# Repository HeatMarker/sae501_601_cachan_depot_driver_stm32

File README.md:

# Projet STM32

Ce dépôt contient l'intégralité du code source et la documentation pour le projet STM32.

## Structure du projet

* **Racine** : Contient le projet STM32 complet (fichiers sources, includes, configuration).
* **datasheet/** : Contient la documentation technique générée (Doxygen/Datasheet).

---

## Documentation

La documentation se trouve dans le dossier `datasheet/`. Deux formats sont proposés, mais la **version HTML est fortement recommandée** pour la navigation.

### 1. Version HTML (Recommandée) 
Format le plus pratique pour explorer le code et les fonctions.

* **Emplacement :** Ouvrir le fichier `index.html` situé dans le dossier `datasheet/html/`.
* **⚠️ Attention à l'affichage :**
    > Si le texte est illisible ou apparaît "noir sur noir", cela est probablement dû à une extension de mode sombre (Dark Reader, Dark Mode natif, etc.).
    > **Désactiver le mode sombre du navigateur** pour consulter cette documentation correctement.

### 2. Version PDF
Une version PDF est normalement disponible à la racine du dossier `datasheet/`.

**Si le fichier PDF n'est pas présent**, il est nécessaire de le générer via LaTeX :

1.  Se rendre dans le dossier : `datasheet/latex/`
2.  Compiler le fichier source : `refman.tex`
3.  Le fichier généré sera disponible ici : `datasheet/latex/refman.pdf`

---

## Utilisation

1.  Cloner ce dépôt.
2.  Ouvrir le projet avec l'IDE habituel (ex: STM32CubeIDE).
3.  Consulter la documentation HTML dans `datasheet/html/` pour les détails d'implémentation.

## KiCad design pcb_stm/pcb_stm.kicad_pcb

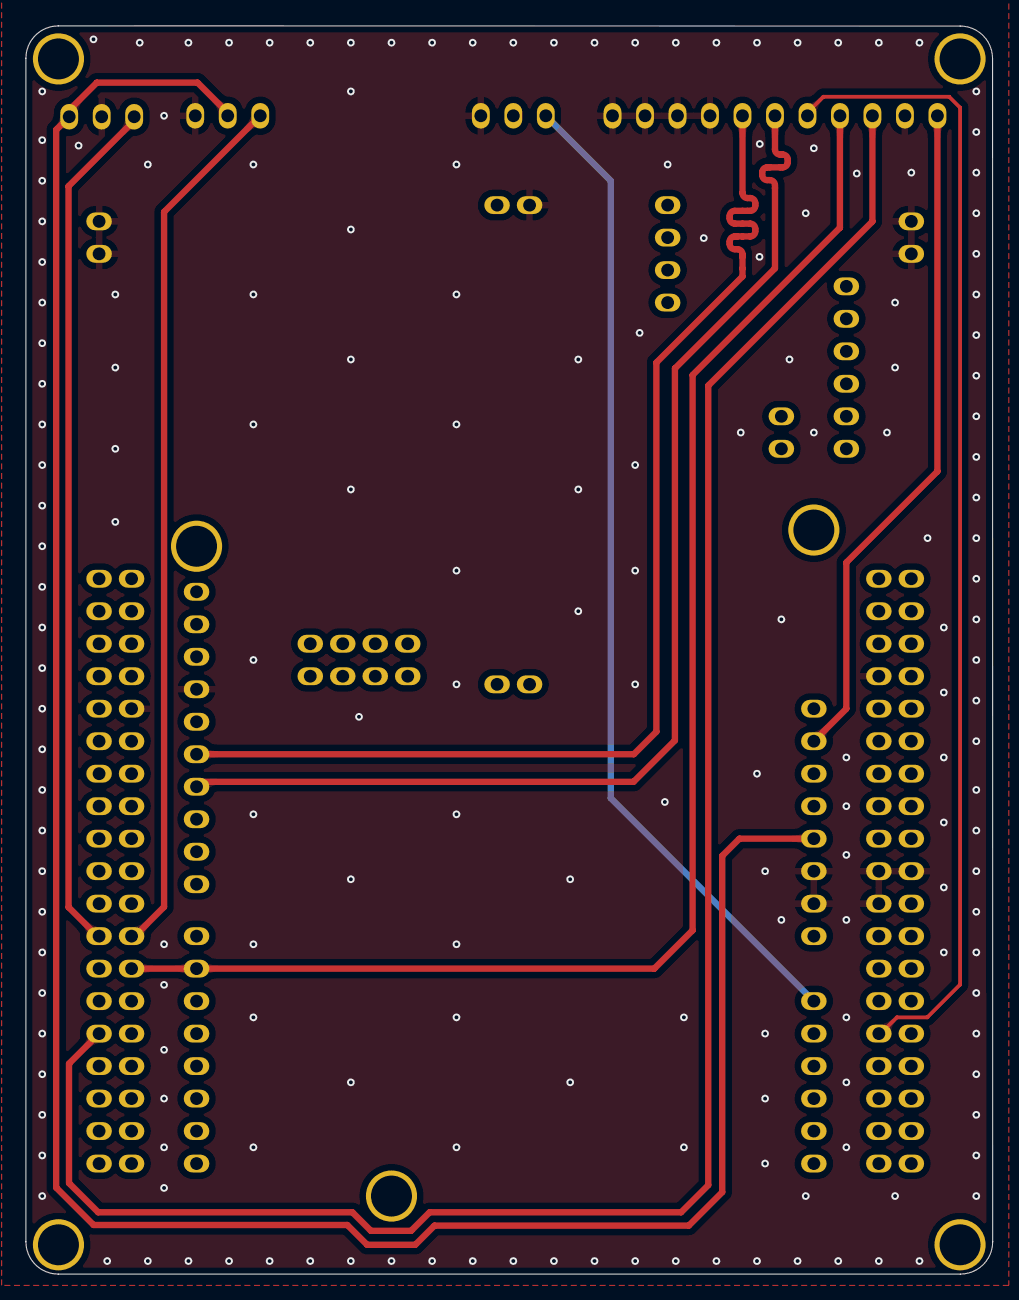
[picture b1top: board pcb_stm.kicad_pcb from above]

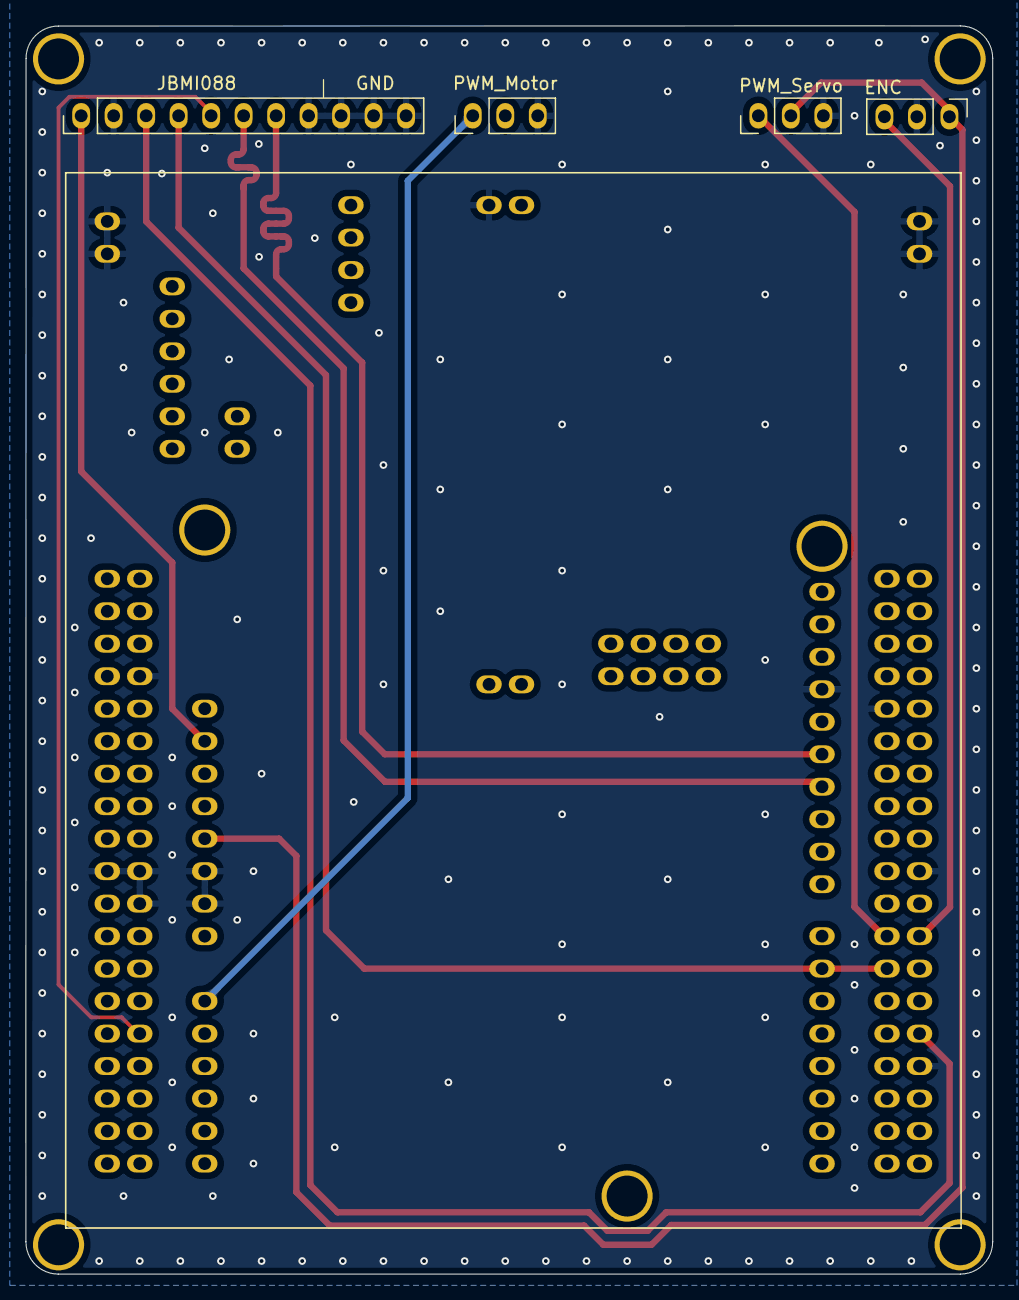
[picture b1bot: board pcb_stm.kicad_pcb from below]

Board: 2 copper layers, 75.6 x 97.6 mm, 5 parts (5 on the bottom side), 11 nets.

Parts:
ENC: Conn_01x03; PinHeader_1x03_P2.54mm_Vertical
JBMI088: Conn_01x11; PinHeader_1x11_P2.54mm_Vertical
PWM_Motor: Conn_01x03; PinHeader_1x03_P2.54mm_Vertical
PWM_Servo: Conn_01x03; PinHeader_1x03_P2.54mm_Vertical
U1: NUCLEO-G0B1RE; MODULE_NUCLEO-G0B1RE

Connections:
+3V3: JBMI088.1, U1.CN6_2 (3V3), U1.CN6_4 (3V3), U1.CN7_12 (3V3), U1.CN7_16 (3V3), U1.JP3_2 (3V3)
+5V: ENC.1, PWM_Servo.2, U1.CN6_5 (5V), U1.CN7_18 (5V), U1.JP2_2 (5V), U1.JP2_4 (5V), U1.JP2_6 (5V), U1.JP2_8 (5V)
CSB1: JBMI088.3, U1.CN10_30 (PB13)
CSB2: JBMI088.4, U1.CN9_7 (PB14), U1.CN10_25 (PB14)
ENC: ENC.3, U1.CN10_24 (PB6)
GND: ENC.2, JBMI088.2, JBMI088.8, JBMI088.9, JBMI088.10, JBMI088.11, PWM_Motor.3, PWM_Servo.3, U1.CN5_7 (AGND), U1.CN6_6 (GND), U1.CN6_7 (GND), U1.CN7_8 (GND), U1.CN7_19 (GND), U1.CN7_20 (GND), U1.CN7_22 (GND), U1.CN10_9 (AGND), U1.CN10_20 (GND), U1.CN10_32 (AGND), U1.JP1_2 (GND), U1.JP4_1 (GND), U1.JP4_2 (GND), U1.JP5_1 (GND), U1.JP5_2 (GND)
MISO: JBMI088.7, U1.CN5_5 (PA6), U1.CN10_13 (PA6)
MOSI: JBMI088.6, U1.CN5_4 (PA7), U1.CN10_15 (PA7)
PWM_MOT: PWM_Motor.1, U1.CN7_28 (PA0), U1.CN8_1 (PA0)
PWM_SERVO: PWM_Servo.1, U1.CN9_8 (PA8), U1.CN10_23 (PA8)
SCK: JBMI088.5, U1.CN7_30 (PA1), U1.CN8_2 (PA1)

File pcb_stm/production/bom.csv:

Designator,Footprint,Quantity,Value,LCSC Part #
"_4, _3, _2, ",,4,,
"ENC, PWM_MOTOR, PWM_SERVO",PinHeader_1x03_P2.54mm_Vertical,3,Conn_01x03,
JBMI088,PinHeader_1x11_P2.54mm_Vertical,1,Conn_01x11,
U1,MODULE_NUCLEO-G0B1RE,1,NUCLEO-G0B1RE,

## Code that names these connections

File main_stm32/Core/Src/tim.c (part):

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
    __HAL_RCC_GPIOB_CLK_ENABLE();
    /**TIM4 GPIO Configuration
    PB6     ------> TIM4_CH1
    */
    GPIO_InitStruct.Pin = GPIO_PIN_6;
    GPIO_InitStruct.Mode = GPIO_MODE_AF_PP;
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  /* USER CODE END TIM1_MspPostInit 0 */
    __HAL_RCC_GPIOA_CLK_ENABLE();
    /**TIM1 GPIO Configuration
    PA8     ------> TIM1_CH1
    */
    GPIO_InitStruct.Pin = PWM_servo_Pin;
    GPIO_InitStruct.Mode = GPIO_MODE_AF_PP;
    GPIO_InitStruct.Pull = GPIO_NOPULL;
    GPIO_InitStruct.Speed = GPIO_SPEED_FREQ_LOW;
    GPIO_InitStruct.Alternate = GPIO_AF2_TIM1;
    HAL_GPIO_Init(PWM_servo_GPIO_Port, &GPIO_InitStruct);

  /* USER CODE BEGIN TIM1_MspPostInit 1 */

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
    __HAL_RCC_GPIOA_CLK_ENABLE();
    /**TIM2 GPIO Configuration
    PA0     ------> TIM2_CH1
    */
    GPIO_InitStruct.Pin = PWM_motor_Pin;
    GPIO_InitStruct.Mode = GPIO_MODE_AF_PP;
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    __HAL_RCC_TIM4_CLK_DISABLE();

    /**TIM4 GPIO Configuration
    PB6     ------> TIM4_CH1
    */
    HAL_GPIO_DeInit(GPIOB, GPIO_PIN_6);

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
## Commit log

2026-02-04 Revise README for STM32 project and documentation
    Updated project description and added documentation details.
2026-02-04 push du local

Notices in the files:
main_stm32/Core/Src/tim.c:
Copyright (c) 2025 STMicroelectronics.
All rights reserved.
This software is licensed under terms that can be found in the LICENSE file
